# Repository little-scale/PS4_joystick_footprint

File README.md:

# PS4_joystick_footprint
PS4 Joystick Footprint for Kicad

This footprint has been tested using a breakout PCB, whch is also available here

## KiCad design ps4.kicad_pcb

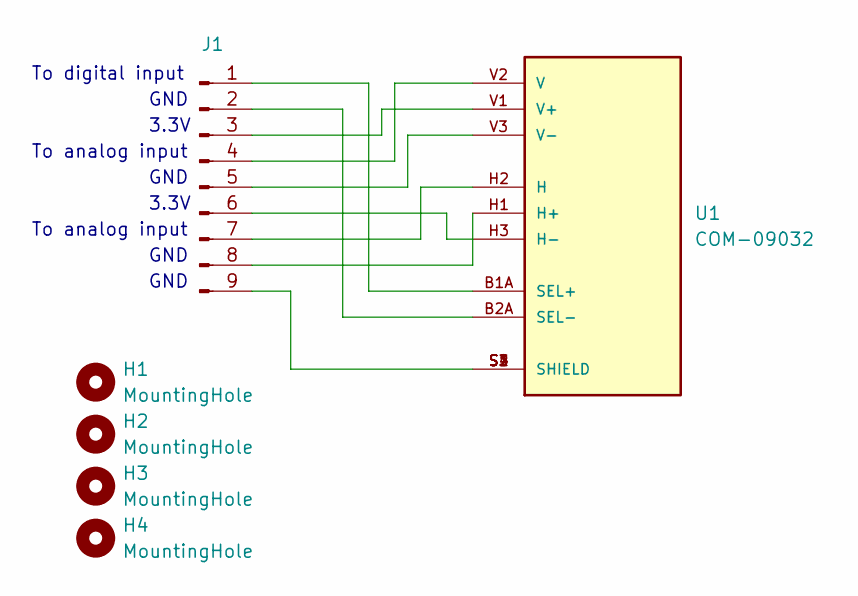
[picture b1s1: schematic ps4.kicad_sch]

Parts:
H1, H2, H3, H4: MountingHole; MountingHole_3.2mm_M3_DIN965
J1: Conn_01x05_Male; PinHeader_1x09_P2.54mm_Vertical
U1: COM-09032; XDCR_COM-09032; PARTREV N/A

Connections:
unnamed: J1.3, U1.V1 (V+)
unnamed: J1.4, U1.V2 (V)
unnamed: J1.5, U1.V3 (V-)
unnamed: J1.6, U1.H3 (H-)
unnamed: J1.7, U1.H2 (H)
unnamed: J1.8, U1.H1 (H+)
unnamed: J1.9, U1.S1 (SHIELD), U1.S2 (SHIELD), U1.S3 (SHIELD), U1.S4 (SHIELD)
unnamed: J1.1, U1.B1A (SEL+)
unnamed: J1.2, U1.B2A (SEL-)

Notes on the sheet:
GND
3.3V
To digital input
To analog input

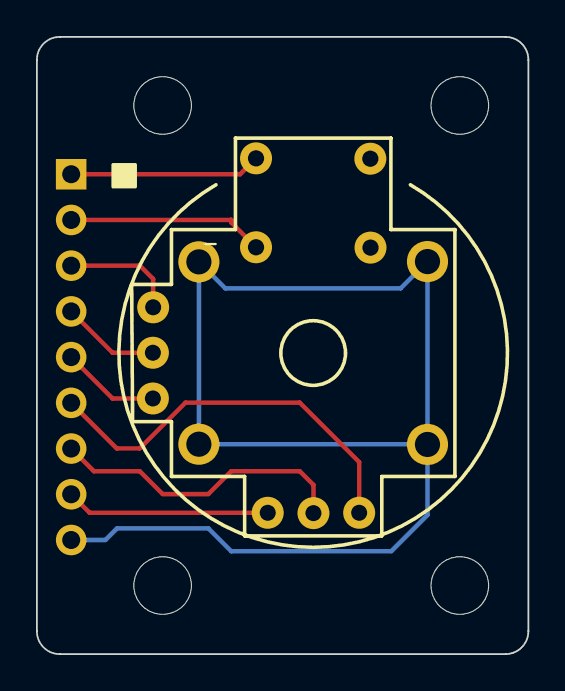
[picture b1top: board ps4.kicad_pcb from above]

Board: 2 copper layers, 27.3 x 34.3 mm, 6 parts (1 on the bottom side), 9 nets.
